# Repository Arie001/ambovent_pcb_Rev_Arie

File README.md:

# ambovent_pcb_Rev_Arie
This is a PCB  make in Kicad that is made to combine most of the design of the open project
Very Much work in Progress  

I have Just Change  the Direction of the Connectors and added a Securing Point  
the Gerbers Are Not Up todate 

It is 3:30 Am

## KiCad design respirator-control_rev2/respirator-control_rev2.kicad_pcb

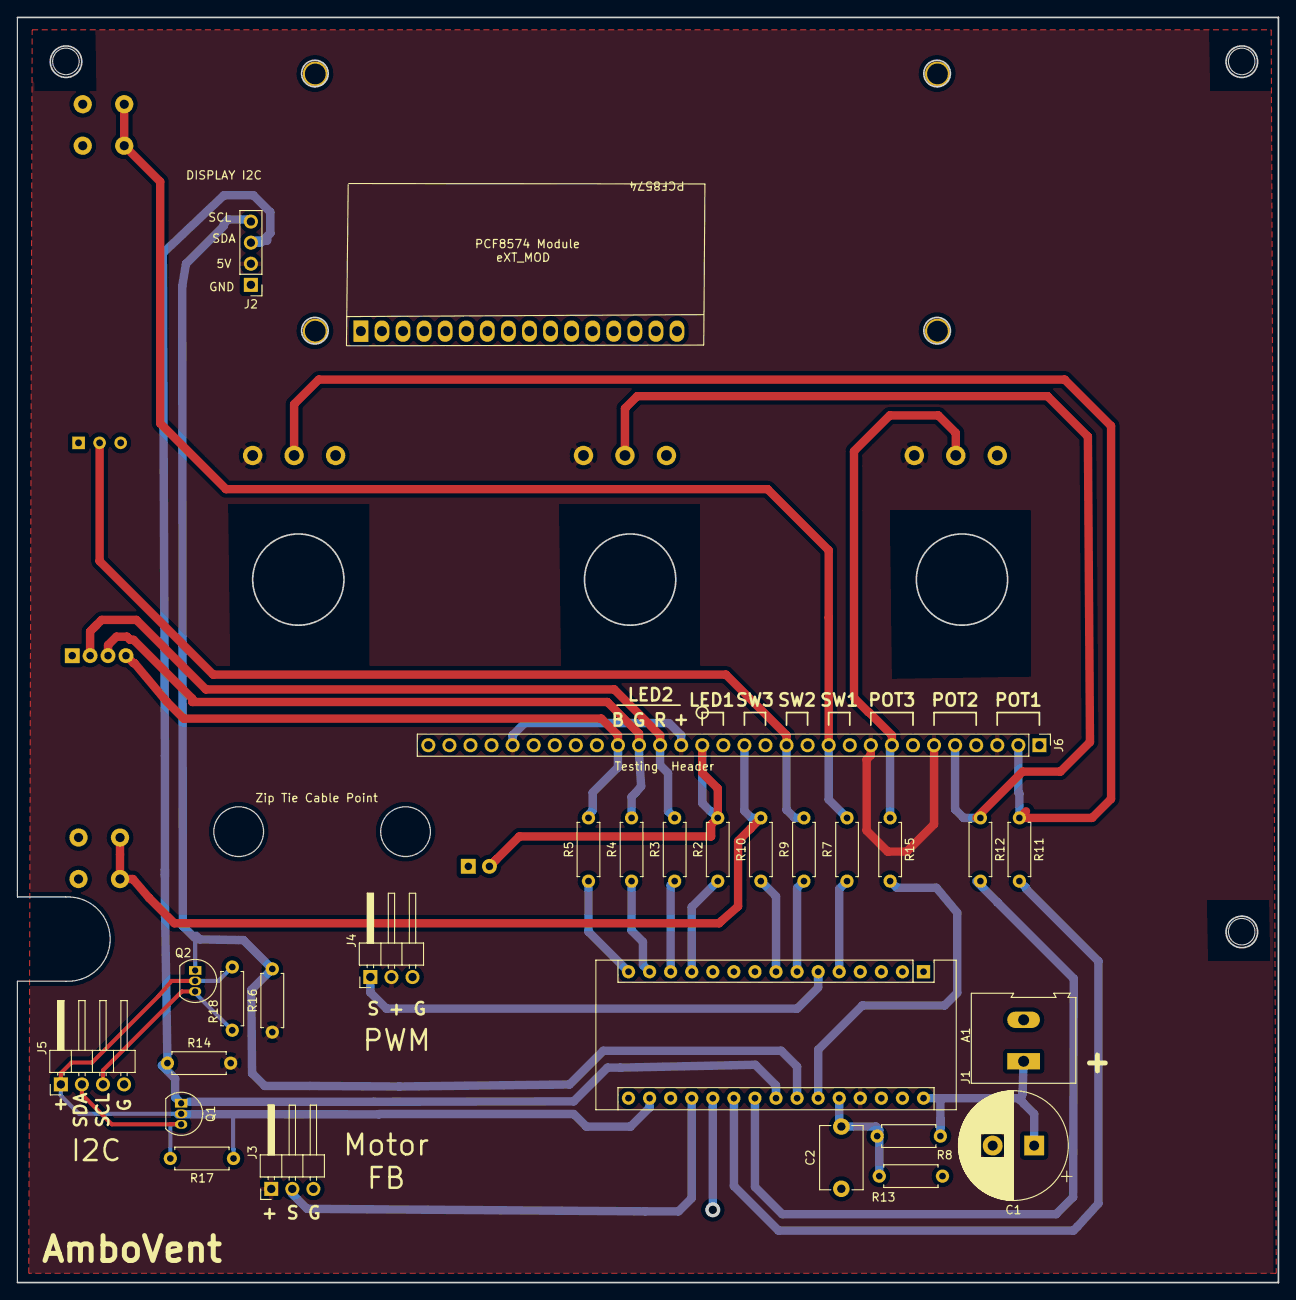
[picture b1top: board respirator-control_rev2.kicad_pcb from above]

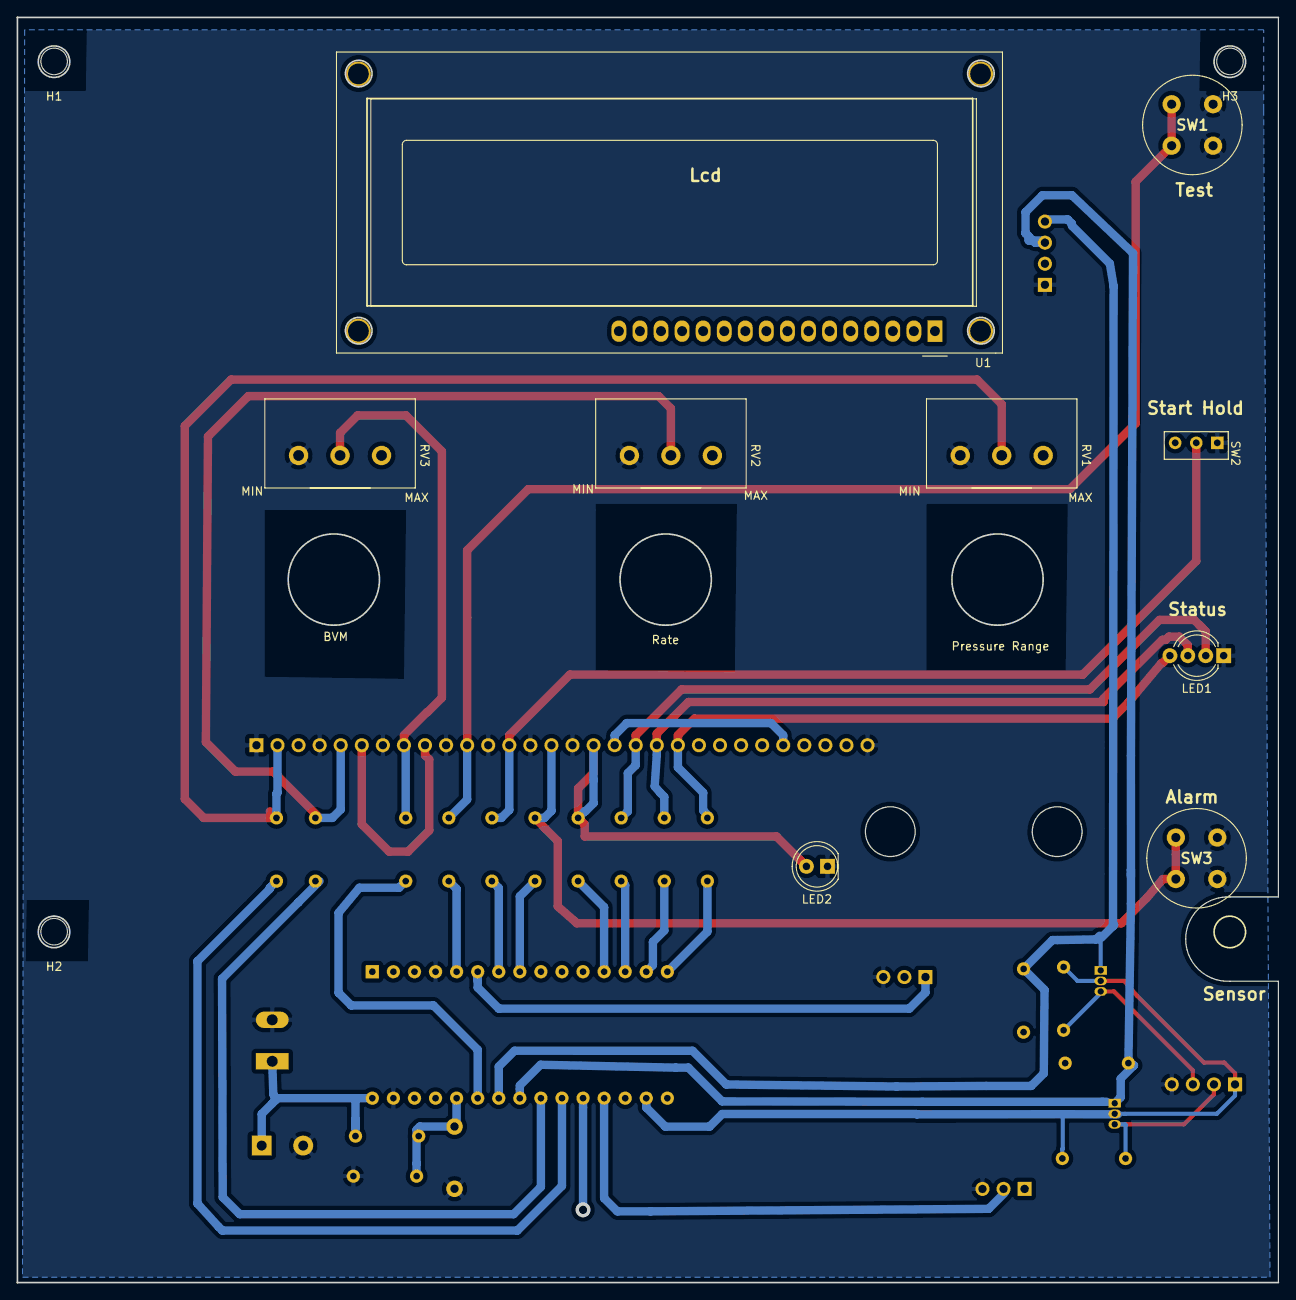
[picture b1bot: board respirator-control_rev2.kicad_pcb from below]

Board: 2 copper layers, 152.0 x 152.5 mm, 40 parts (12 on the bottom side), 31 nets.

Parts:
A1: Arduino_Nano_v3.x; Arduino_Nano
C1: CP; CP_Radial_D13.0mm_P5.00mm
C2: 100nf; C_Disc_D7.5mm_W5.0mm_P7.50mm
H1, H2, H3: MountingHole; MountingHole_3.2mm_M3
J1: Conn_01x02; TerminalBlock_Altech_AK300-2_P5.00mm
J2: Header 1X4; PinHeader_1x04_P2.54mm_Vertical
J3, J4: Header 1X3; PinHeader_1x03_P2.54mm_Horizontal
J5: Header 1X4; PinHeader_1x04_P2.54mm_Horizontal
J6: Header 1X30; PinHeader_1x30_P2.54mm_Vertical
LED1: LED_CRGB; LED_D5.0mm-4_RGB_Wide_Pins
LED2: LED; LED_D5.0mm_Clear
Q1, Q2: 2N7000; TO-92_Inline
R2, R3, R4, R5, R7, R9, R10, R11, R12, R15: 100; R_Axial_DIN0207_L6.3mm_D2.5mm_P7.62mm_Horizontal
R8, R14, R16, R17, R18: 10k; R_Axial_DIN0207_L6.3mm_D2.5mm_P7.62mm_Horizontal
R13: 2k; R_Axial_DIN0207_L6.3mm_D2.5mm_P7.62mm_Horizontal
RV1, RV2, RV3: R_POT; Potentiometer_old_school
SW1, SW3: SW_Push_Dual; D6R00F2LFS
SW2: SW_Push; eswitch_200MSP
U1: LCD-016N002L; WC1602A
eXT_MOD: i2c-1602

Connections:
+3V3: A1.17, J5.1, Q1.2, Q2.2, R17.1, R18.1
+5V: A1.27, J2.2, J3.1, J4.2, J6.3, J6.6, J6.9, J6.18, J6.26, R14.1, R16.1, RV1.3, RV2.3, RV3.3
/12v_Check: A1.26, C2.2, R8.2, R13.1
/CT1: J6.2, R11.1, RV1.2
/CT2: J6.5, R12.1, RV2.2
/CT3: J6.8, R15.1, RV3.2
/LED1: J6.17, LED2.2, R2.2
/LED2_B: J6.21, LED1.4, R5.2
/LED2_G: J6.20, LED1.3, R4.2
/LED2_R: J6.19, LED1.2, R3.2
/MOTOR_FB: A1.19, J3.2
/MOTOR_PWM: A1.6, J4.1
/SCL: A1.24, J2.4, Q2.1, R16.2
/SCL_3V3: J5.3, Q2.3, R18.2
/SDA: A1.23, J2.3, Q1.1, R14.2
/SDA_3V3: J5.2, Q1.3, R17.2
/SW1: J6.11, R7.2, SW1.2, SW1.4
/SW2: J6.13, R9.2, SW2.2
/SW3: J6.15, R10.2, SW3.2, SW3.4
/Vin: A1.30, C1.1, J1.1, R8.1
GND: A1.4, A1.29, C1.2, C2.1, J1.2, J2.1, J3.3, J4.3, J5.4, J6.1, J6.4, J6.7, J6.10, J6.12, J6.14, J6.16, J6.30, LED1.1, LED2.1, R13.2, RV1.1, RV2.1, RV3.1, SW1.1, SW1.3, SW2.1, SW3.1, SW3.3
unnamed: A1.5, R7.1
unnamed: A1.7, R9.1
unnamed: A1.8, R10.1
unnamed: A1.12, R2.1
unnamed: A1.13, R3.1
unnamed: A1.14, R4.1
unnamed: A1.15, R5.1
unnamed: A1.21, R11.2
unnamed: A1.22, R12.2
unnamed: A1.25, R15.2

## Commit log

2020-04-13 Add files via upload
    Change Connectors to horizontal from veritical add Point To secure Cables .
    add JPG to Sch to show How to secure Cables.
    Gerber in Not Updated and Not Checked In Fusion .
2020-05-04 Add files via upload
    Add level convert SCL SDA
